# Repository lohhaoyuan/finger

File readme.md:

**finger.**

completely screwed robocup team

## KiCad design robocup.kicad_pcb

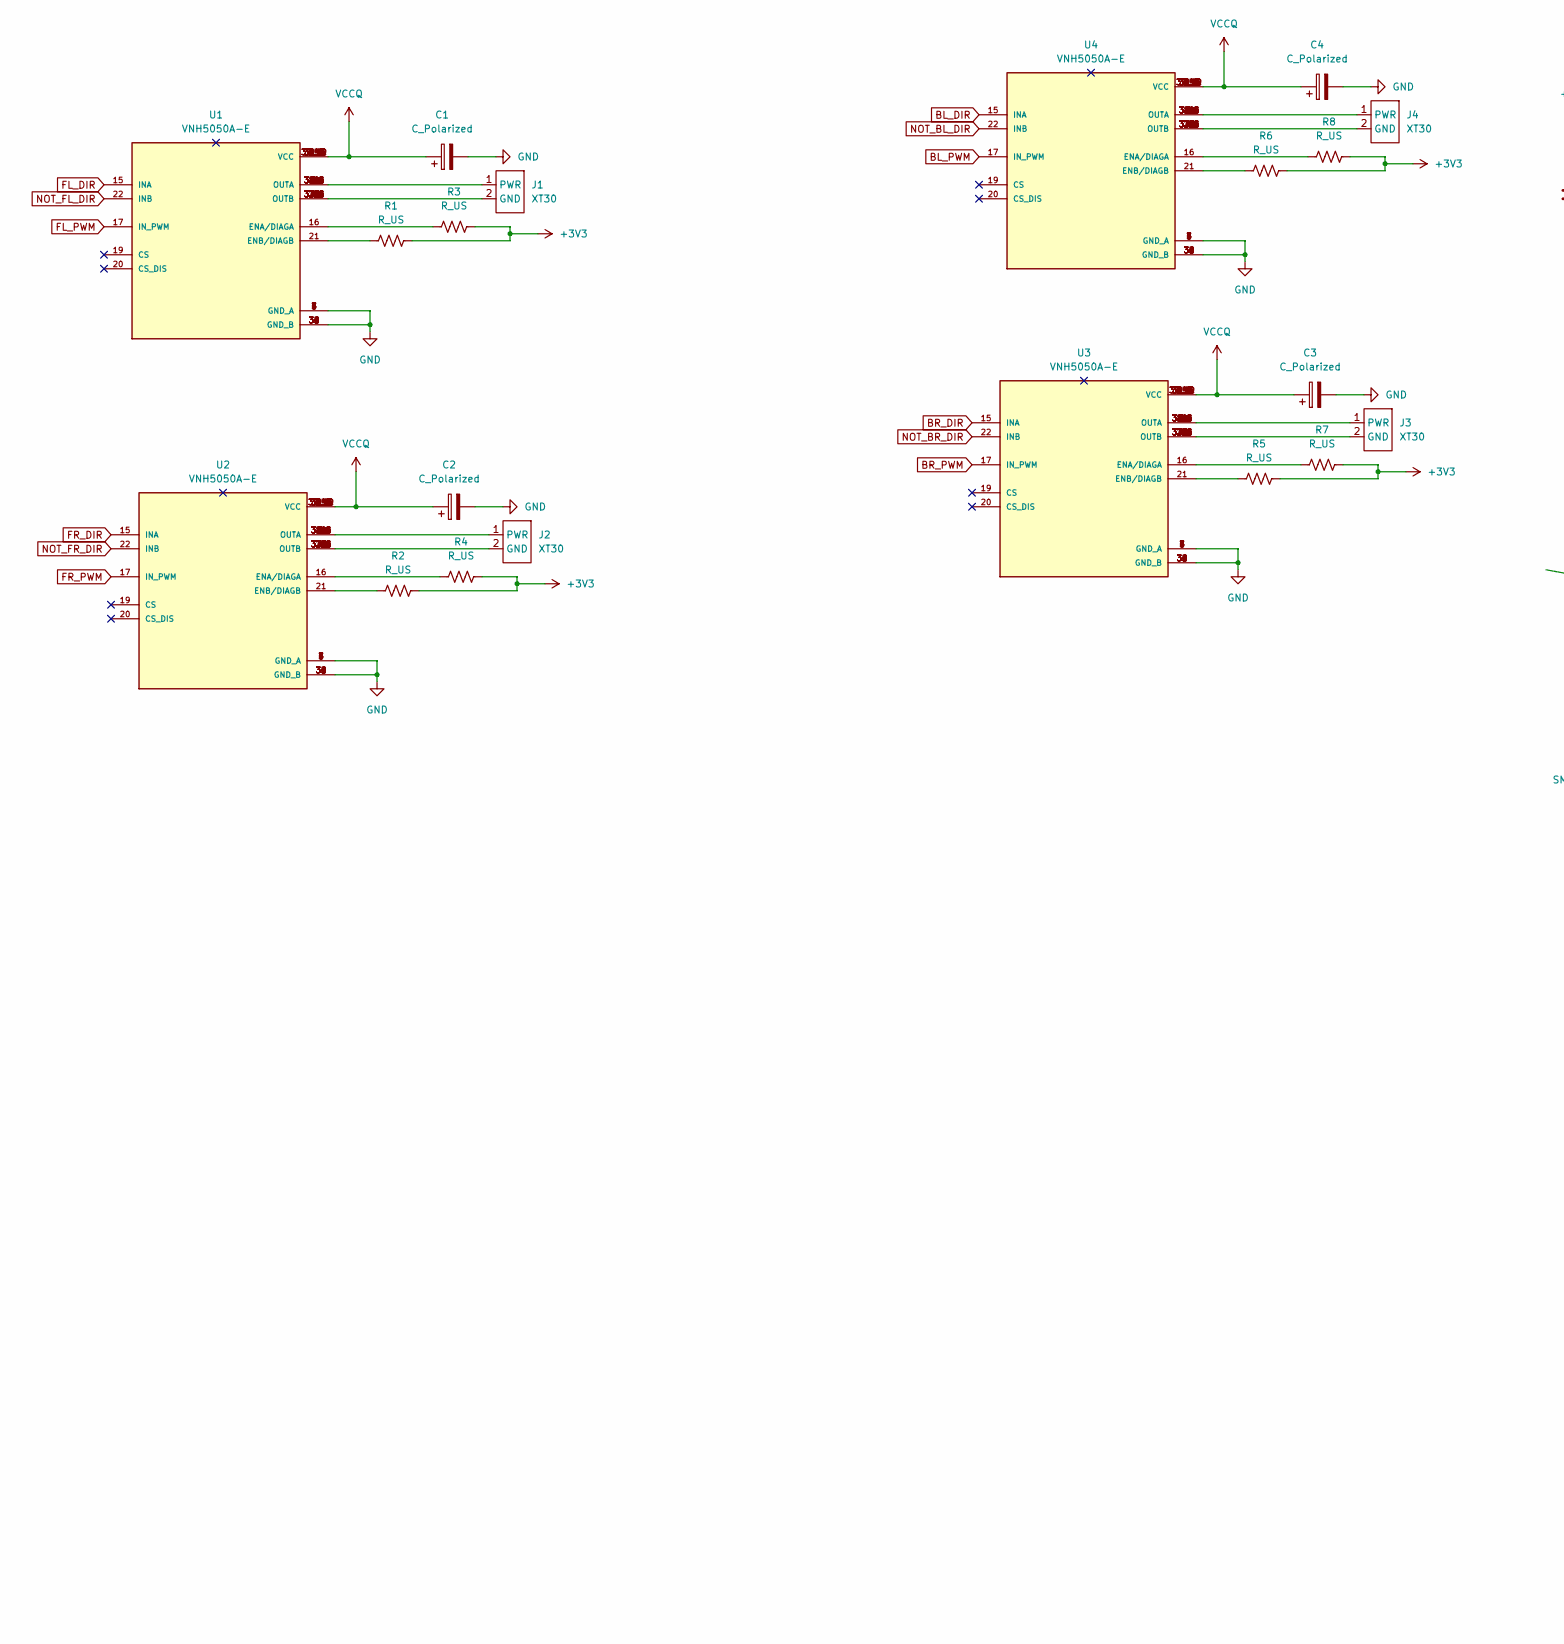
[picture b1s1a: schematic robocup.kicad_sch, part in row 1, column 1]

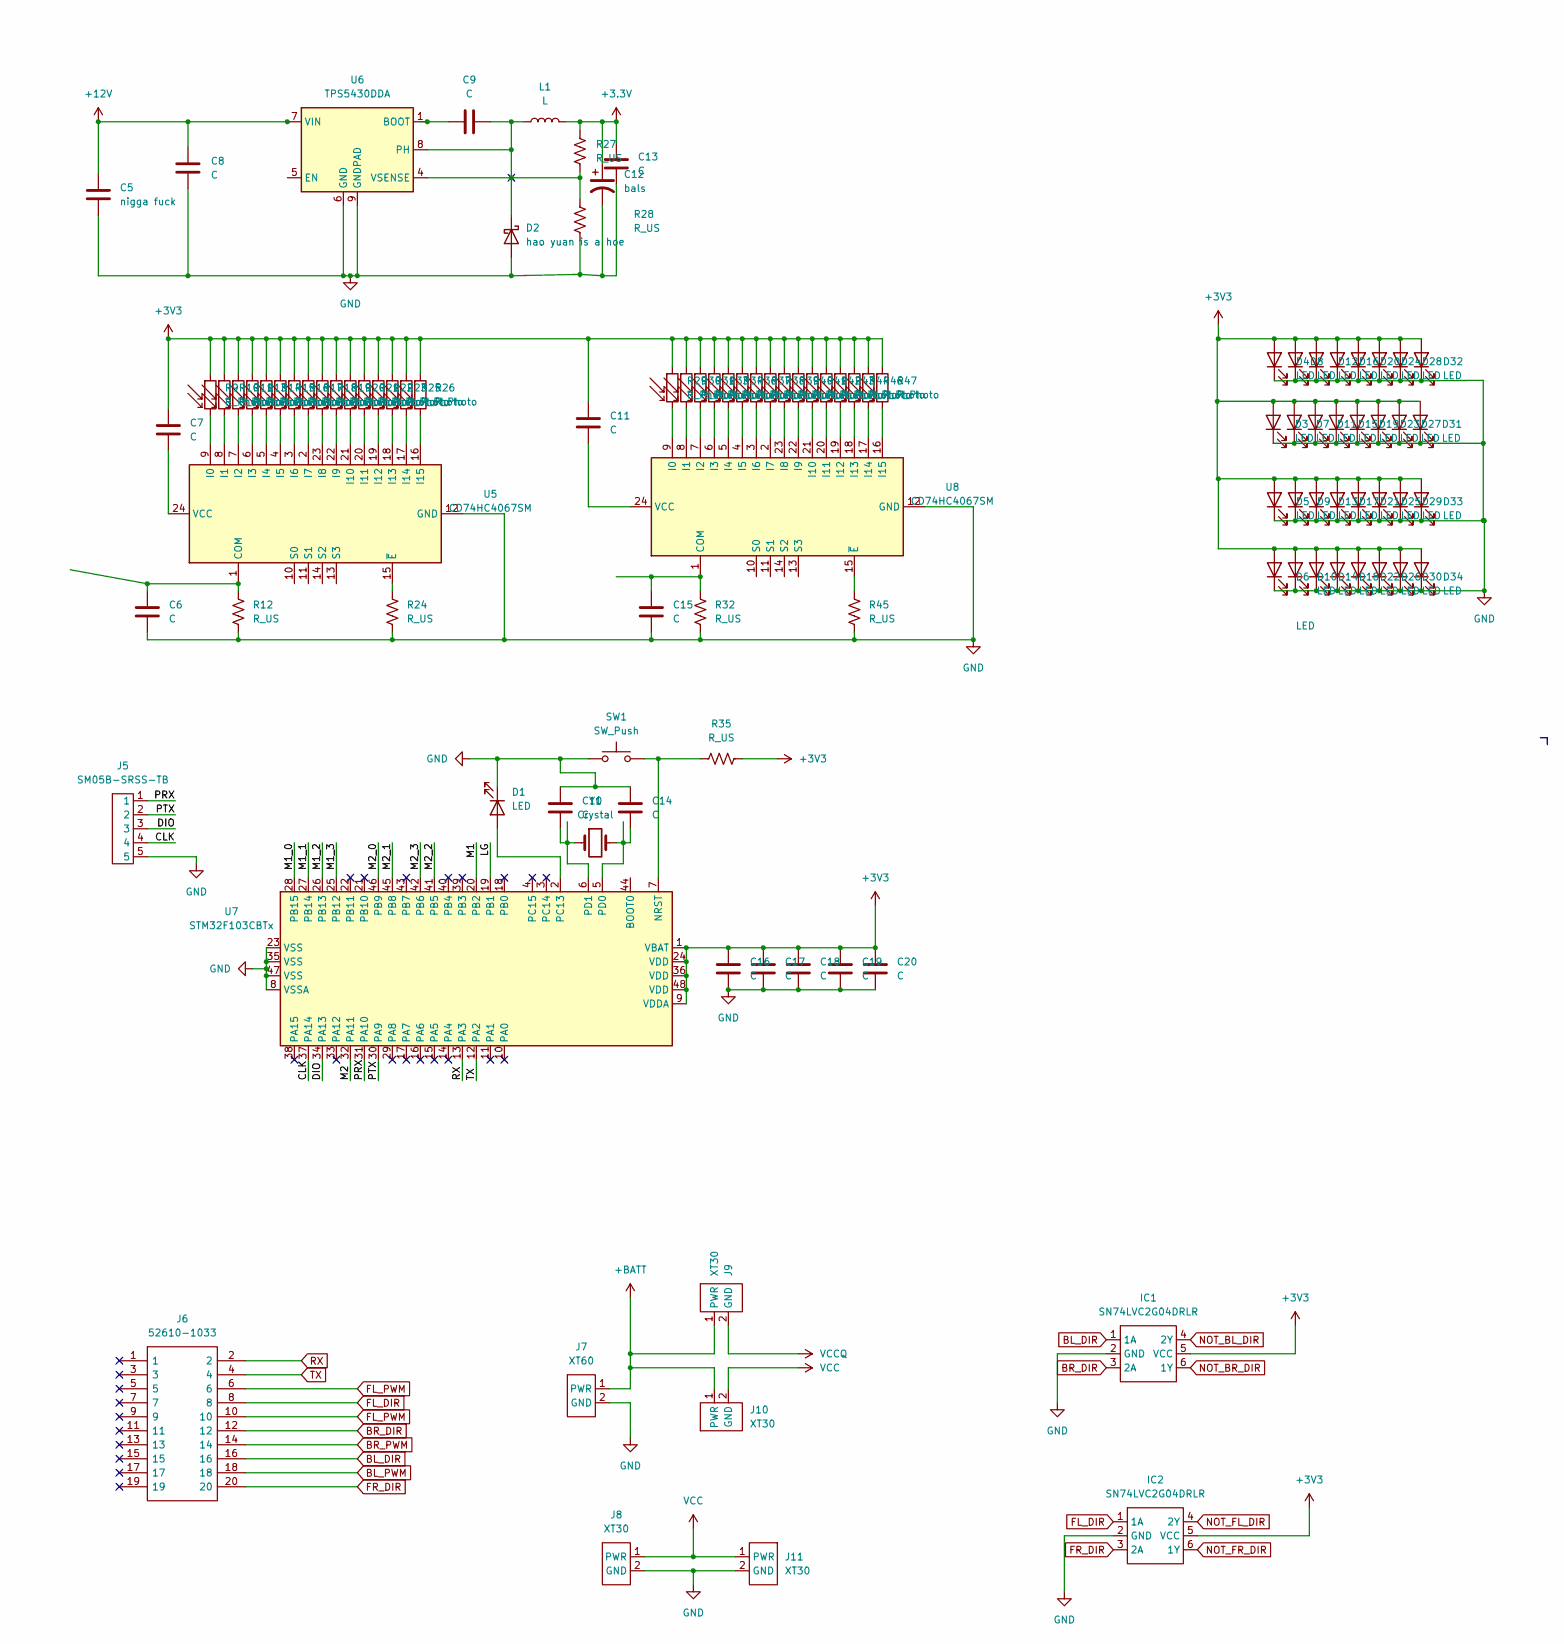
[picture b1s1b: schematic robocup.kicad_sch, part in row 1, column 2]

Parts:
C1, C2, C3, C4: C_Polarized; CAPCP7361X380N
C5: nigga fuck; C_0603_1608Metric_Pad1.08x0.95mm_HandSolder
C6, C7, C10, C11, C14, C15, C16, C17, C18, C19, C20: C; C_0201_0603Metric_Pad0.64x0.40mm_HandSolder
C8, C9, C13: C; C_0603_1608Metric_Pad1.08x0.95mm_HandSolder
C12: bals; C_0603_1608Metric_Pad1.08x0.95mm_HandSolder
D1, D3, D4, D5, D6, D7, D8, D9, D10, D11, D12, D13, D14, D15, D16, D17, D18, D19, D20, D21, D22, D23, D24, D25, D26, D27, D28, D29, D30, D31, D32, D33, D34: LED; LED_0603_1608Metric_Pad1.05x0.95mm_HandSolder
D2: hao yuan is a hoe; D_0603_1608Metric_Pad1.05x0.95mm_HandSolder
IC1, IC2: SN74LVC2G04DRLR; SOT95P280X145-6N
J1, J2, J3, J4, J8, J9, J10, J11: XT30; AMASS_XT30U-M_1x02_P5.0mm_Vertical
J5: SM05B-SRSS-TB; JST-SR-SIDE-5
J6: 52610-1033; Manufacturer_Part_Number 52610-1033; Mouser Part Number 538-52610-1033
J7: XT60; AMASS_XT60-M_1x02_P7.20mm_Vertical
L1: L; L_0603_1608Metric_Pad1.05x0.95mm_HandSolder
R1, R2, R3, R4, R5, R6, R7, R8, R12, R24, R27, R28, R32, R35, R45: R_US; R_0603_1608Metric_Pad0.98x0.95mm_HandSolder
R9, R10, R11, R13, R14, R15, R16, R17, R18, R19, R20, R21, R22, R23, R25, R26, R29, R30, R31, R33, R34, R36, R37, R38, R39, R40, R41, R42, R43, R44, R46, R47: R_Photo; R_0603_1608Metric_Pad0.98x0.95mm_HandSolder
SW1: SW_Push; SW_PUSH_6mm_H7.3mm
U1, U2, U3, U4: VNH5050A-E; SOP50P1030X247-39N; PARTREV 1.0
U5, U8: CD74HC4067SM; SSOP-24_5.3x8.2mm_P0.65mm
U6: TPS5430DDA; TI_SO-PowerPAD-8_ThermalVias
U7: STM32F103CBTx; LQFP-48_7x7mm_P0.5mm
Y1: Crystal; Crystal_SMD_0603-4Pin_6.0x3.5mm_HandSoldering

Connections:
+3.3V: C12.1, C13.1, L1.2, R27.1
+3V3: C7.1, C11.1, C16.1, C17.1, C18.1, C19.1, C20.1, D3.2 (A), D4.2 (A), D5.2 (A), D6.2 (A), D7.2 (A), D8.2 (A), D9.2 (A), D10.2 (A), D11.2 (A), D12.2 (A), D13.2 (A), D14.2 (A), D15.2 (A), D16.2 (A), D17.2 (A), D18.2 (A), D19.2 (A), D20.2 (A), D21.2 (A), D22.2 (A), D23.2 (A), D24.2 (A), D25.2 (A), D26.2 (A), D27.2 (A), D28.2 (A), D29.2 (A), D30.2 (A), D31.2 (A), D32.2 (A), D33.2 (A), D34.2 (A), IC1.5 (VCC), IC2.5 (VCC), R1.2, R2.2, R3.2, R4.2, R5.2, R6.2, R7.2, R8.2, R9.1, R10.1, R11.1, R13.1, R14.1, R15.1, R16.1, R17.1, R18.1, R19.1, R20.1, R21.1, R22.1, R23.1, R25.1, R26.1, R29.1, R30.1, R31.1, R33.1, R34.1, R35.2, R36.1, R37.1, R38.1, R39.1, R40.1, R41.1, R42.1, R43.1, R44.1, R46.1, R47.1, U7.1 (VBAT), U7.9 (VDDA), U7.24 (VDD), U7.36 (VDD), U7.48 (VDD)
+12V: C5.1, C8.1, U6.7 (VIN)
+BATT: J7.1 (PWR), J9.1 (PWR), J10.1 (PWR)
/CLK: J5.4, U7.37 (PA14)
/DIO: J5.3, U7.34 (PA13)
/LG: U7.19 (PB1)
/M1: U7.20 (PB2)
/M1_0: U7.28 (PB15)
/M1_1: U7.27 (PB14)
/M1_2: U7.26 (PB13)
/M1_3: U7.25 (PB12)
/M2: U7.32 (PA11)
/M2_0: U7.46 (PB9)
/M2_1: U7.45 (PB8)
/M2_2: U7.41 (PB5)
/M2_3: U7.42 (PB6)
/PRX: J5.1, U7.31 (PA10)
/PTX: J5.2, U7.30 (PA9)
BL_DIR: IC1.1 (1A), J6.16, U4.15 (INA)
BL_PWM: J6.18, U4.17 (IN_PWM)
BR_DIR: IC1.3 (2A), J6.12, U3.15 (INA)
BR_PWM: J6.14, U3.17 (IN_PWM)
FL_DIR: IC2.1 (1A), J6.8, U1.15 (INA)
FL_PWM: J6.6, J6.10, U1.17 (IN_PWM)
FR_DIR: IC2.3 (2A), J6.20, U2.15 (INA)
FR_PWM: U2.17 (IN_PWM)
GND: C1.2, C2.2, C3.2, C4.2, C5.2, C6.2, C8.2, C10.1, C12.2, C13.2, C14.1, C15.2, C16.2, C17.2, C18.2, C19.2, C20.2, D1.1 (K), D2.2 (A), D3.1 (K), D4.1 (K), D5.1 (K), D6.1 (K), D7.1 (K), D8.1 (K), D9.1 (K), D10.1 (K), D11.1 (K), D12.1 (K), D13.1 (K), D14.1 (K), D15.1 (K), D16.1 (K), D17.1 (K), D18.1 (K), D19.1 (K), D20.1 (K), D21.1 (K), D22.1 (K), D23.1 (K), D24.1 (K), D25.1 (K), D26.1 (K), D27.1 (K), D28.1 (K), D29.1 (K), D30.1 (K), D31.1 (K), D32.1 (K), D33.1 (K), D34.1 (K), IC1.2 (GND), IC2.2 (GND), J5.5, J7.2 (GND), J8.2 (GND), J11.2 (GND), R12.2, R24.2, R28.2, R32.2, R45.2, SW1.1, U1.1 (GND_A), U1.3 (GND_A), U1.4 (GND_A), U1.5 (GND_A), U1.6 (GND_A), U1.7 (GND_A), U1.30 (GND_B), U1.31 (GND_B), U1.32 (GND_B), U1.33 (GND_B), U1.34 (GND_B), U1.36 (GND_B), U2.1 (GND_A), U2.3 (GND_A), U2.4 (GND_A), U2.5 (GND_A), U2.6 (GND_A), U2.7 (GND_A), U2.30 (GND_B), U2.31 (GND_B), U2.32 (GND_B), U2.33 (GND_B), U2.34 (GND_B), U2.36 (GND_B), U3.1 (GND_A), U3.3 (GND_A), U3.4 (GND_A), U3.5 (GND_A), U3.6 (GND_A), U3.7 (GND_A), U3.30 (GND_B), U3.31 (GND_B), U3.32 (GND_B), U3.33 (GND_B), U3.34 (GND_B), U3.36 (GND_B), U4.1 (GND_A), U4.3 (GND_A), U4.4 (GND_A), U4.5 (GND_A), U4.6 (GND_A), U4.7 (GND_A), U4.30 (GND_B), U4.31 (GND_B), U4.32 (GND_B), U4.33 (GND_B), U4.34 (GND_B), U4.36 (GND_B), U5.12 (GND), U6.6 (GND), U6.9 (GNDPAD), U7.8 (VSSA), U7.23 (VSS), U7.35 (VSS), U7.47 (VSS), U8.12 (GND)
NOT_BL_DIR: IC1.4 (2Y), U4.22 (INB)
NOT_BR_DIR: IC1.6 (1Y), U3.22 (INB)
NOT_FL_DIR: IC2.4 (2Y), U1.22 (INB)
NOT_FR_DIR: IC2.6 (1Y), U2.22 (INB)
unnamed: C6.1, R12.1, U5.1 (COM)
unnamed: C7.2, U5.24 (VCC)
unnamed: C9.2, U6.1 (BOOT)
unnamed: C10.2, U7.6 (PD1), Y1.1
unnamed: C11.2, U8.24 (VCC)
unnamed: C14.2, U7.5 (PD0), Y1.2
unnamed: C15.1, R32.1, U8.1 (COM)
unnamed: D1.2 (A), U7.2 (PC13)
unnamed: J1.1 (PWR), U1.2 (OUTA), U1.8 (OUTA), U1.9 (OUTA), U1.10 (OUTA), U1.11 (OUTA), U1.12 (OUTA), U1.14 (OUTA), U1.38 (OUTA), U1.38_1 (OUTA), U1.38_2 (OUTA), U1.38_3 (OUTA), U1.38_4 (OUTA), U1.38_5 (OUTA), U1.38_6 (OUTA)
unnamed: J1.2 (GND), U1.23 (OUTB), U1.25 (OUTB), U1.26 (OUTB), U1.27 (OUTB), U1.28 (OUTB), U1.29 (OUTB), U1.35 (OUTB), U1.37 (OUTB), U1.37_1 (OUTB), U1.37_2 (OUTB), U1.37_3 (OUTB), U1.37_4 (OUTB), U1.37_5 (OUTB), U1.37_6 (OUTB)
unnamed: J2.1 (PWR), U2.2 (OUTA), U2.8 (OUTA), U2.9 (OUTA), U2.10 (OUTA), U2.11 (OUTA), U2.12 (OUTA), U2.14 (OUTA), U2.38 (OUTA), U2.38_1 (OUTA), U2.38_2 (OUTA), U2.38_3 (OUTA), U2.38_4 (OUTA), U2.38_5 (OUTA), U2.38_6 (OUTA)
unnamed: J2.2 (GND), U2.23 (OUTB), U2.25 (OUTB), U2.26 (OUTB), U2.27 (OUTB), U2.28 (OUTB), U2.29 (OUTB), U2.35 (OUTB), U2.37 (OUTB), U2.37_1 (OUTB), U2.37_2 (OUTB), U2.37_3 (OUTB), U2.37_4 (OUTB), U2.37_5 (OUTB), U2.37_6 (OUTB)
unnamed: J3.1 (PWR), U3.2 (OUTA), U3.8 (OUTA), U3.9 (OUTA), U3.10 (OUTA), U3.11 (OUTA), U3.12 (OUTA), U3.14 (OUTA), U3.38 (OUTA), U3.38_1 (OUTA), U3.38_2 (OUTA), U3.38_3 (OUTA), U3.38_4 (OUTA), U3.38_5 (OUTA), U3.38_6 (OUTA)
unnamed: J3.2 (GND), U3.23 (OUTB), U3.25 (OUTB), U3.26 (OUTB), U3.27 (OUTB), U3.28 (OUTB), U3.29 (OUTB), U3.35 (OUTB), U3.37 (OUTB), U3.37_1 (OUTB), U3.37_2 (OUTB), U3.37_3 (OUTB), U3.37_4 (OUTB), U3.37_5 (OUTB), U3.37_6 (OUTB)
unnamed: J4.1 (PWR), U4.2 (OUTA), U4.8 (OUTA), U4.9 (OUTA), U4.10 (OUTA), U4.11 (OUTA), U4.12 (OUTA), U4.14 (OUTA), U4.38 (OUTA), U4.38_1 (OUTA), U4.38_2 (OUTA), U4.38_3 (OUTA), U4.38_4 (OUTA), U4.38_5 (OUTA), U4.38_6 (OUTA)
unnamed: J4.2 (GND), U4.23 (OUTB), U4.25 (OUTB), U4.26 (OUTB), U4.27 (OUTB), U4.28 (OUTB), U4.29 (OUTB), U4.35 (OUTB), U4.37 (OUTB), U4.37_1 (OUTB), U4.37_2 (OUTB), U4.37_3 (OUTB), U4.37_4 (OUTB), U4.37_5 (OUTB), U4.37_6 (OUTB)
unnamed: R1.1, U1.21 (ENB/DIAGB)
unnamed: R2.1, U2.21 (ENB/DIAGB)
unnamed: R3.1, U1.16 (ENA/DIAGA)
unnamed: R4.1, U2.16 (ENA/DIAGA)
unnamed: R5.1, U3.21 (ENB/DIAGB)
unnamed: R6.1, U4.21 (ENB/DIAGB)
unnamed: R7.1, U3.16 (ENA/DIAGA)
unnamed: R8.1, U4.16 (ENA/DIAGA)
unnamed: R9.2, U5.9 (I0)
unnamed: R10.2, U5.8 (I1)
unnamed: R11.2, U5.7 (I2)
unnamed: R13.2, U5.6 (I3)
unnamed: R14.2, U5.5 (I4)
unnamed: R15.2, U5.4 (I5)
unnamed: R16.2, U5.3 (I6)
unnamed: R17.2, U5.2 (I7)
unnamed: R18.2, U5.23 (I8)
unnamed: R19.2, U5.22 (I9)
unnamed: R20.2, U5.21 (I10)
unnamed: R21.2, U5.20 (I11)
unnamed: R22.2, U5.19 (I12)
unnamed: R23.2, U5.18 (I13)
unnamed: R24.1, U5.15 (~E)
unnamed: R25.2, U5.17 (I14)
unnamed: R26.2, U5.16 (I15)
unnamed: R29.2, U8.9 (I0)
unnamed: R30.2, U8.8 (I1)
unnamed: R31.2, U8.7 (I2)
unnamed: R33.2, U8.6 (I3)
unnamed: R34.2, U8.5 (I4)
unnamed: R35.1, SW1.2, U7.7 (NRST)
unnamed: R36.2, U8.4 (I5)
unnamed: R37.2, U8.3 (I6)
unnamed: R38.2, U8.2 (I7)
unnamed: R39.2, U8.23 (I8)
unnamed: R40.2, U8.22 (I9)
unnamed: R41.2, U8.21 (I10)
unnamed: R42.2, U8.20 (I11)
unnamed: R43.2, U8.19 (I12)
unnamed: R44.2, U8.18 (I13)
unnamed: R45.1, U8.15 (~E)
unnamed: R46.2, U8.17 (I14)
unnamed: R47.2, U8.16 (I15)
RX: U7.13 (PA3)
TX: U7.12 (PA2)
VCC: J8.1 (PWR), J10.2 (GND), J11.1 (PWR)
VCCQ: C1.1, C2.1, C3.1, C4.1, J9.2 (GND), U1.13 (VCC), U1.24 (VCC), U1.39 (VCC), U1.39_1 (VCC), U1.39_2 (VCC), U1.39_3 (VCC), U1.39_4 (VCC), U1.39_5 (VCC), U1.39_6 (VCC), U1.39_7 (VCC), U1.39_8 (VCC), U1.39_9 (VCC), U1.39_10 (VCC), U1.39_11 (VCC), U1.39_12 (VCC), U2.13 (VCC), U2.24 (VCC), U2.39 (VCC), U2.39_1 (VCC), U2.39_2 (VCC), U2.39_3 (VCC), U2.39_4 (VCC), U2.39_5 (VCC), U2.39_6 (VCC), U2.39_7 (VCC), U2.39_8 (VCC), U2.39_9 (VCC), U2.39_10 (VCC), U2.39_11 (VCC), U2.39_12 (VCC), U3.13 (VCC), U3.24 (VCC), U3.39 (VCC), U3.39_1 (VCC), U3.39_2 (VCC), U3.39_3 (VCC), U3.39_4 (VCC), U3.39_5 (VCC), U3.39_6 (VCC), U3.39_7 (VCC), U3.39_8 (VCC), U3.39_9 (VCC), U3.39_10 (VCC), U3.39_11 (VCC), U3.39_12 (VCC), U4.13 (VCC), U4.24 (VCC), U4.39 (VCC), U4.39_1 (VCC), U4.39_2 (VCC), U4.39_3 (VCC), U4.39_4 (VCC), U4.39_5 (VCC), U4.39_6 (VCC), U4.39_7 (VCC), U4.39_8 (VCC), U4.39_9 (VCC), U4.39_10 (VCC), U4.39_11 (VCC), U4.39_12 (VCC)

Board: 2 copper layers, 124 parts (0 on the bottom side), 78 nets, no tracks yet.

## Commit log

2023-04-21 intiiatl
